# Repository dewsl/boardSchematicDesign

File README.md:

# boardSchematicDesign
Schematic , Board and SketchUp Files (sch,brd,skp files)

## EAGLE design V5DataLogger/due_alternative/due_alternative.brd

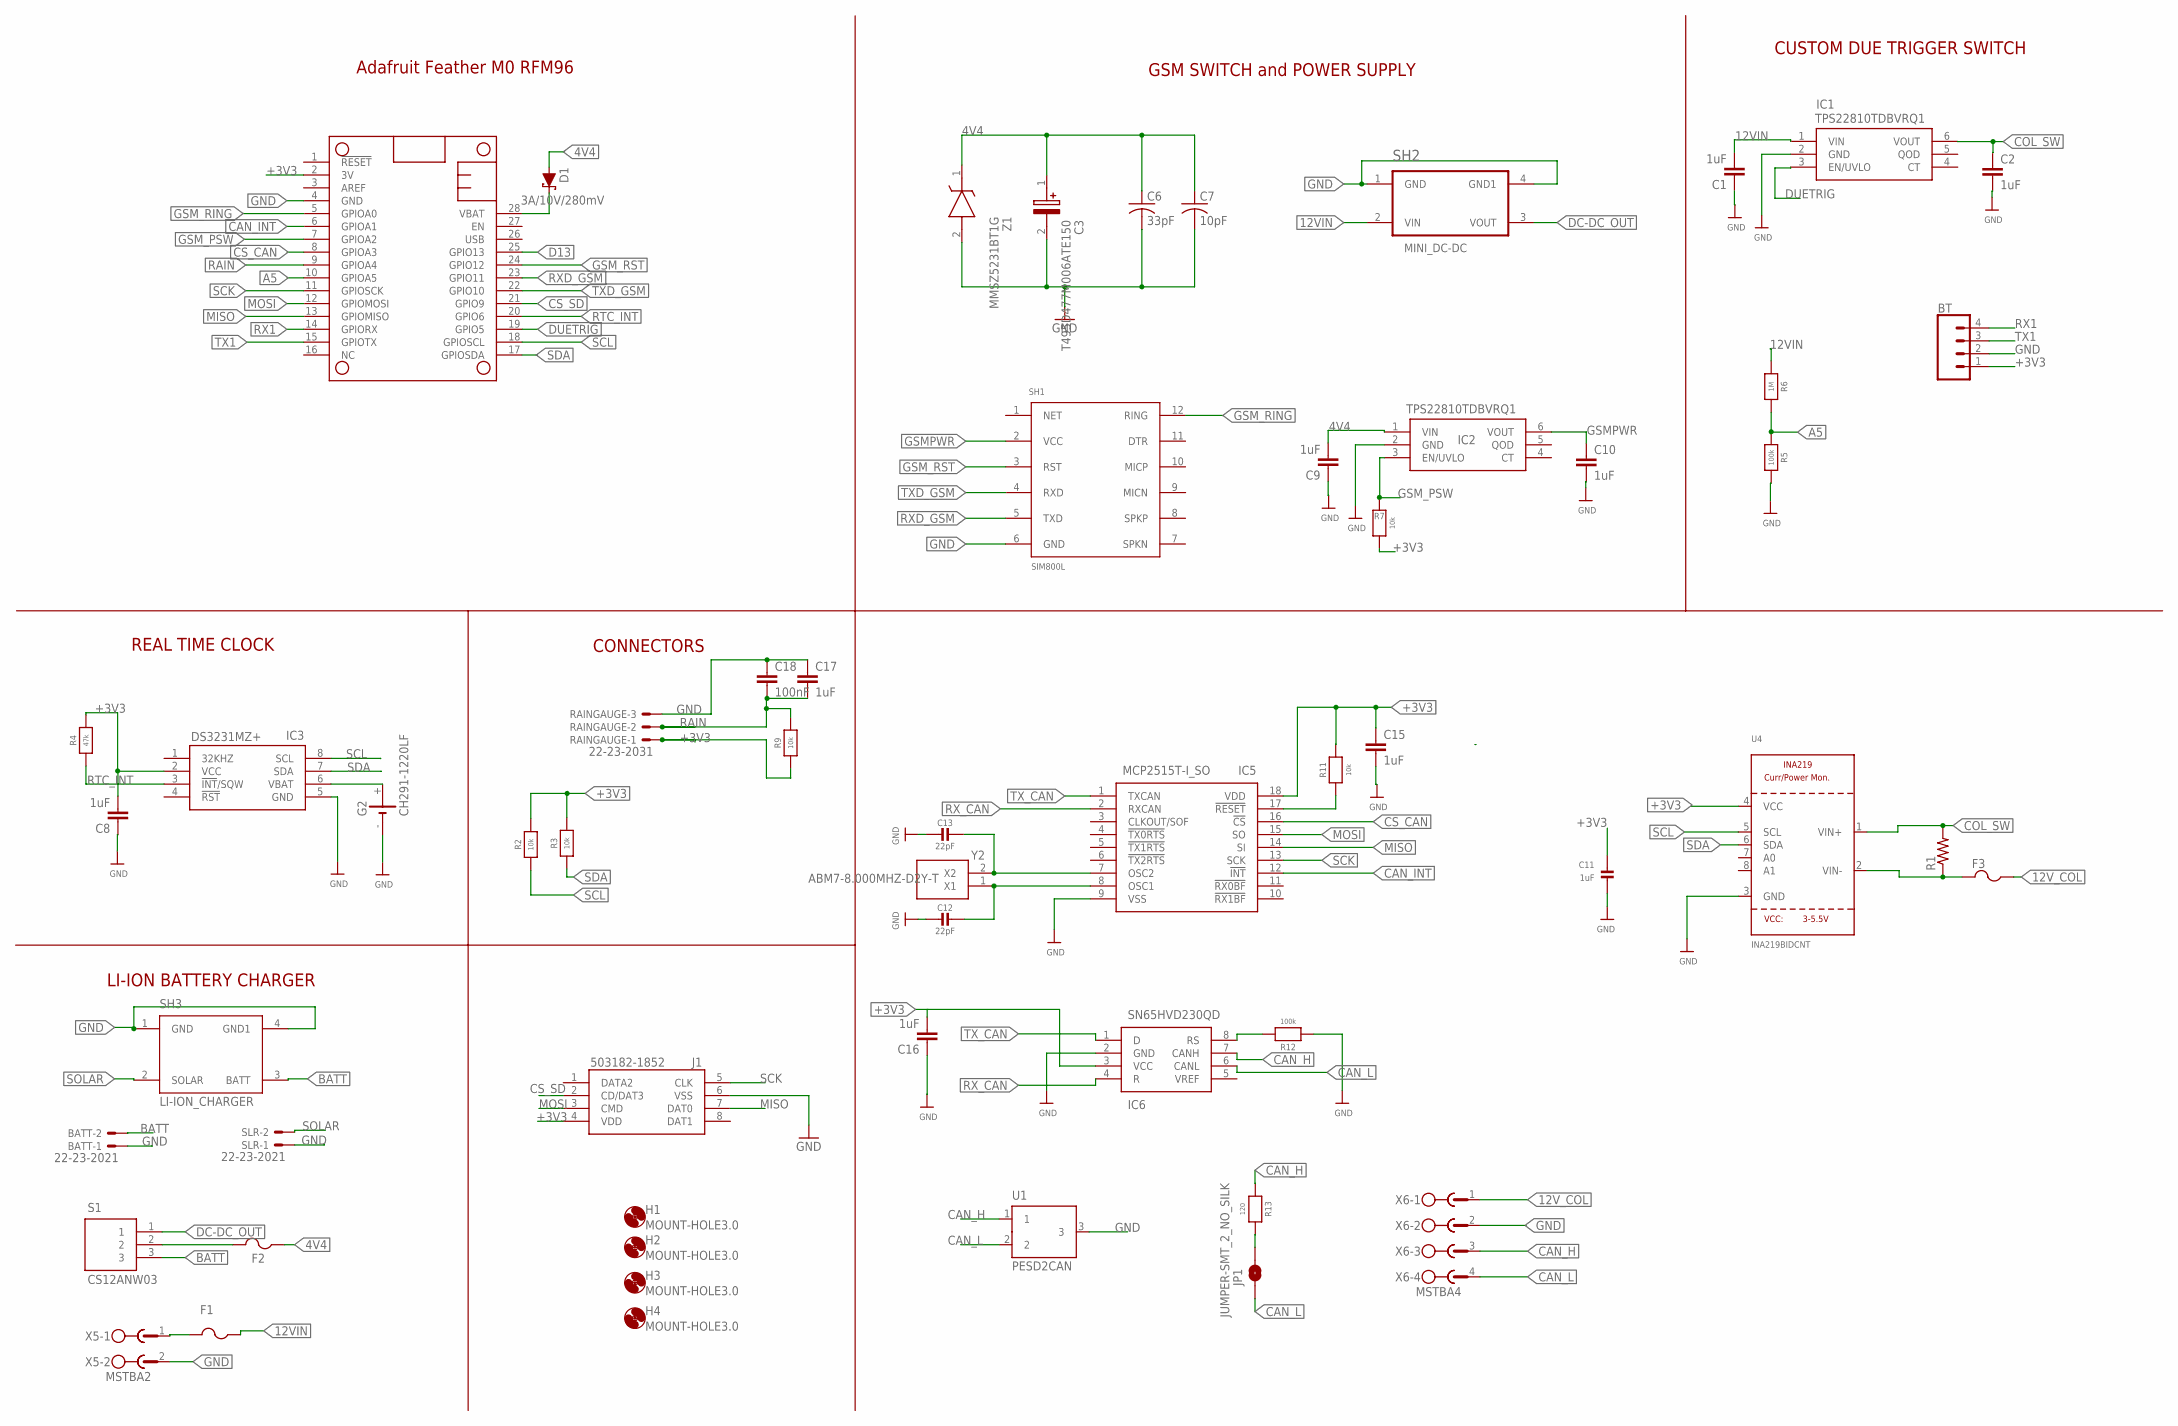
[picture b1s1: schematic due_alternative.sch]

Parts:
BATT: 22-23-2021
BT: CONN_04PTH; 1X04
C1, C2, C8, C9, C10, C15, C16, C17: 1uF; C0603
C3: T495D477M006ATE150; CAPPM7343X310N
C6: 33pF; C0603
C7: 10pF; C0603
C11: 1uF; 0603-NO
C12, C13: 22pF; 0603-NO
C18: 100nF; C0603
D1: 3A/10V/280mV; SOD-323
F1, F2, F3: PTCFUSE-1206; R1206
G2: CH291-1220LF
H1, H2, H3, H4: MOUNT-HOLE3.0; 3,0
IC1, IC2: TPS22810TDBVRQ1; SOT95P280X145-6N
IC3: DS3231MZ+; SOIC127P600X175-8N
IC5: MCP2515T-I_SO; SOIC127P1030X265-18N
IC6: SN65HVD230QD; SOIC127P600X175-8N
J1: 503182-1852; 5031821852
JP1: JUMPER-SMT_2_NO_SILK; SMT-JUMPER_2_NO_SILK
MS1: FEATHERWING_NODIM; FEATHERWING_DIM
R1: R-US_R6332; R6332
R2, R3, R7, R9, R11: 10k; 0603-NO
R4: 47k; 0603-NO
R5, R12: 100k; 0603-NO
R6: 1M; 0603-NO
R13: 120; 0603-NO
RAINGAUGE: 22-23-2031
S1: CS12ANW03
SH1: SIM800L; GSM_SIM800L
SH2: MINI_DC-DC; MINI_DC-DC_MP2307DN
SH3: LI-ION_CHARGER
SLR: 22-23-2021
U1: PESD2CAN; SOT23
U4: INA219BIDCNT; SOT23-8; MPN INA219BIDCNT
X5: MSTBA2
X6: MSTBA4
Y2: ABM7-8.000MHZ-D2Y-T; ABM78000MHZD2YT
Z1: MMSZ5231BT1G; SOD3716X135N

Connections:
4V4: C3.1 (+), C6.1, C7.1, C9.2, D1.A, F2.1, IC2.1 (VIN), Z1.1 (K)
12VIN: C1.2, F1.1, IC1.1 (VIN), R6.1, SH2.2 (VIN)
12V_COL: F3.1, X6.1
+3V3: BT.1, C8.2, C11.1, C15.1, C16.2, IC3.2 (VCC), IC5.18 (VDD), IC6.3 (VCC), J1.4 (VDD), MS1.2 (3V), R2.2, R3.2, R4.2, R7.1, R9.1, R11.2, RAINGAUGE.1, U4.4 (VCC)
A5: MS1.10 (GPIOA5), R5.1, R6.2
BATT: BATT.2, S1.3, SH3.3 (BATT)
CAN_H: IC6.7 (CANH), R13.1, U1.1, X6.3
CAN_INT: IC5.12 (!INT), MS1.6 (GPIOA1)
CAN_L: IC6.6 (CANL), JP1.1, U1.2, X6.4
COL_SW: C2.1, IC1.6 (VOUT), R1.2, U4.1 (VIN+)
CS_CAN: IC5.16 (!CS), MS1.8 (GPIOA3)
CS_SD: J1.2 (CD/DAT3), MS1.21 (GPIO9)
D13: MS1.25 (GPIO13)
DC-DC_OUT: S1.1, SH2.3 (VOUT)
DUETRIG: IC1.3 (EN/UVLO), MS1.19 (GPIO5)
GND: BATT.1, BT.2, C1.1, C2.2, C3.2 (-), C6.2, C7.2, C8.1, C9.1, C10.2, C11.2, C12.2, C13.2, C15.2, C16.1, C17.1, C18.1, G2.-, IC1.2 (GND), IC2.2 (GND), IC3.5 (GND), IC5.9 (VSS), IC6.2 (GND), J1.6 (VSS), MS1.4 (GND), R5.2, R12.1, RAINGAUGE.3, SH1.6 (GND), SH2.1 (GND), SH2.4 (GND1), SH3.1 (GND), SH3.4 (GND1), SLR.1, U1.3, U4.3 (GND), X5.2, X6.2, Z1.2 (A)
GSMPWR: C10.1, IC2.6 (VOUT), SH1.2 (VCC)
GSM_PSW: IC2.3 (EN/UVLO), MS1.7 (GPIOA2), R7.2
GSM_RING: MS1.5 (GPIOA0), SH1.12 (RING)
GSM_RST: MS1.24 (GPIO12), SH1.3 (RST)
MISO: IC5.14 (SI), J1.7 (DAT0), MS1.13 (GPIOMISO)
MOSI: IC5.15 (SO), J1.3 (CMD), MS1.12 (GPIOMOSI)
unnamed: C12.1, IC5.8 (OSC1), Y2.1 (X1)
unnamed: G2.+, IC3.6 (VBAT)
unnamed: C13.1, IC5.7 (OSC2), Y2.2 (X2)
unnamed: F1.2, X5.1
unnamed: IC6.8 (RS), R12.2
unnamed: F3.2, R1.1, U4.2 (VIN-)
unnamed: IC5.17 (!RESET), R11.1
unnamed: JP1.2, R13.2
unnamed: F2.2, S1.2
RAIN: C17.2, C18.2, MS1.9 (GPIOA4), R9.2, RAINGAUGE.2
RTC_INT: IC3.3 (!INT!/SQW), MS1.20 (GPIO6), R4.1
RX1: BT.4, MS1.14 (GPIORX)
RXD_GSM: MS1.23 (GPIO11), SH1.5 (TXD)
RX_CAN: IC5.2 (RXCAN), IC6.4 (R)
SCK: IC5.13 (SCK), J1.5 (CLK), MS1.11 (GPIOSCK)
SCL: IC3.8 (SCL), MS1.18 (GPIOSCL), R2.1, U4.5 (SCL)
SDA: IC3.7 (SDA), MS1.17 (GPIOSDA), R3.1, U4.6 (SDA)
SOLAR: SH3.2 (SOLAR), SLR.2
TX1: BT.3, MS1.15 (GPIOTX)
TXD_GSM: MS1.22 (GPIO10), SH1.4 (RXD)
TX_CAN: IC5.1 (TXCAN), IC6.1 (D)
VBAT: D1.C, MS1.28 (VBAT)

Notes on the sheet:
Adafruit Feather M0 RFM96
GSM SWITCH and POWER SUPPLY
CUSTOM DUE TRIGGER SWITCH
REAL TIME CLOCK
CONNECTORS
LI-ION BATTERY CHARGER

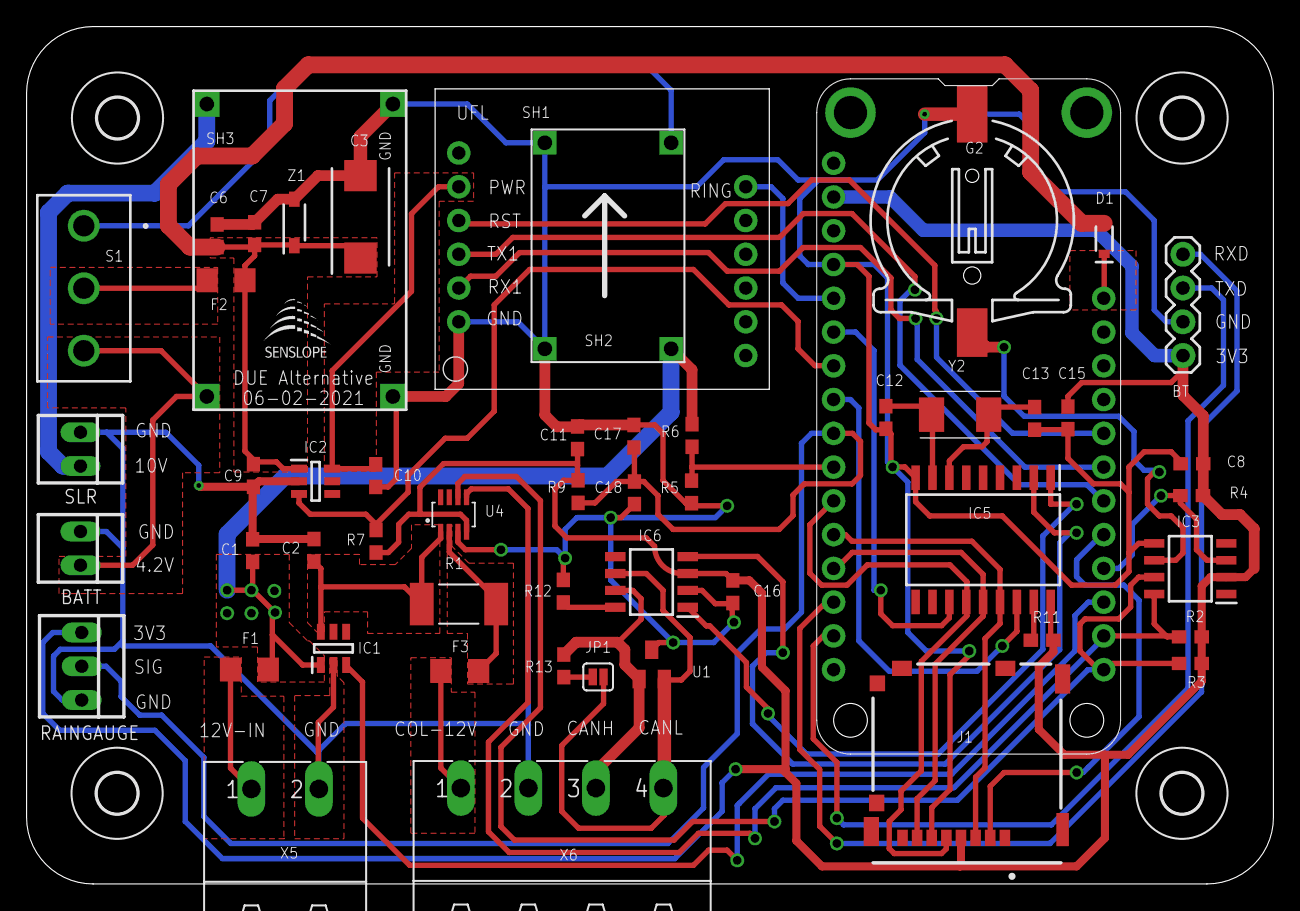
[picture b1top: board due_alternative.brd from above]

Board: 2 copper layers, 93.8 x 64.5 mm, 58 parts (0 on the bottom side), 43 nets.

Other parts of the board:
U$13: LOGO_SML_TNAME

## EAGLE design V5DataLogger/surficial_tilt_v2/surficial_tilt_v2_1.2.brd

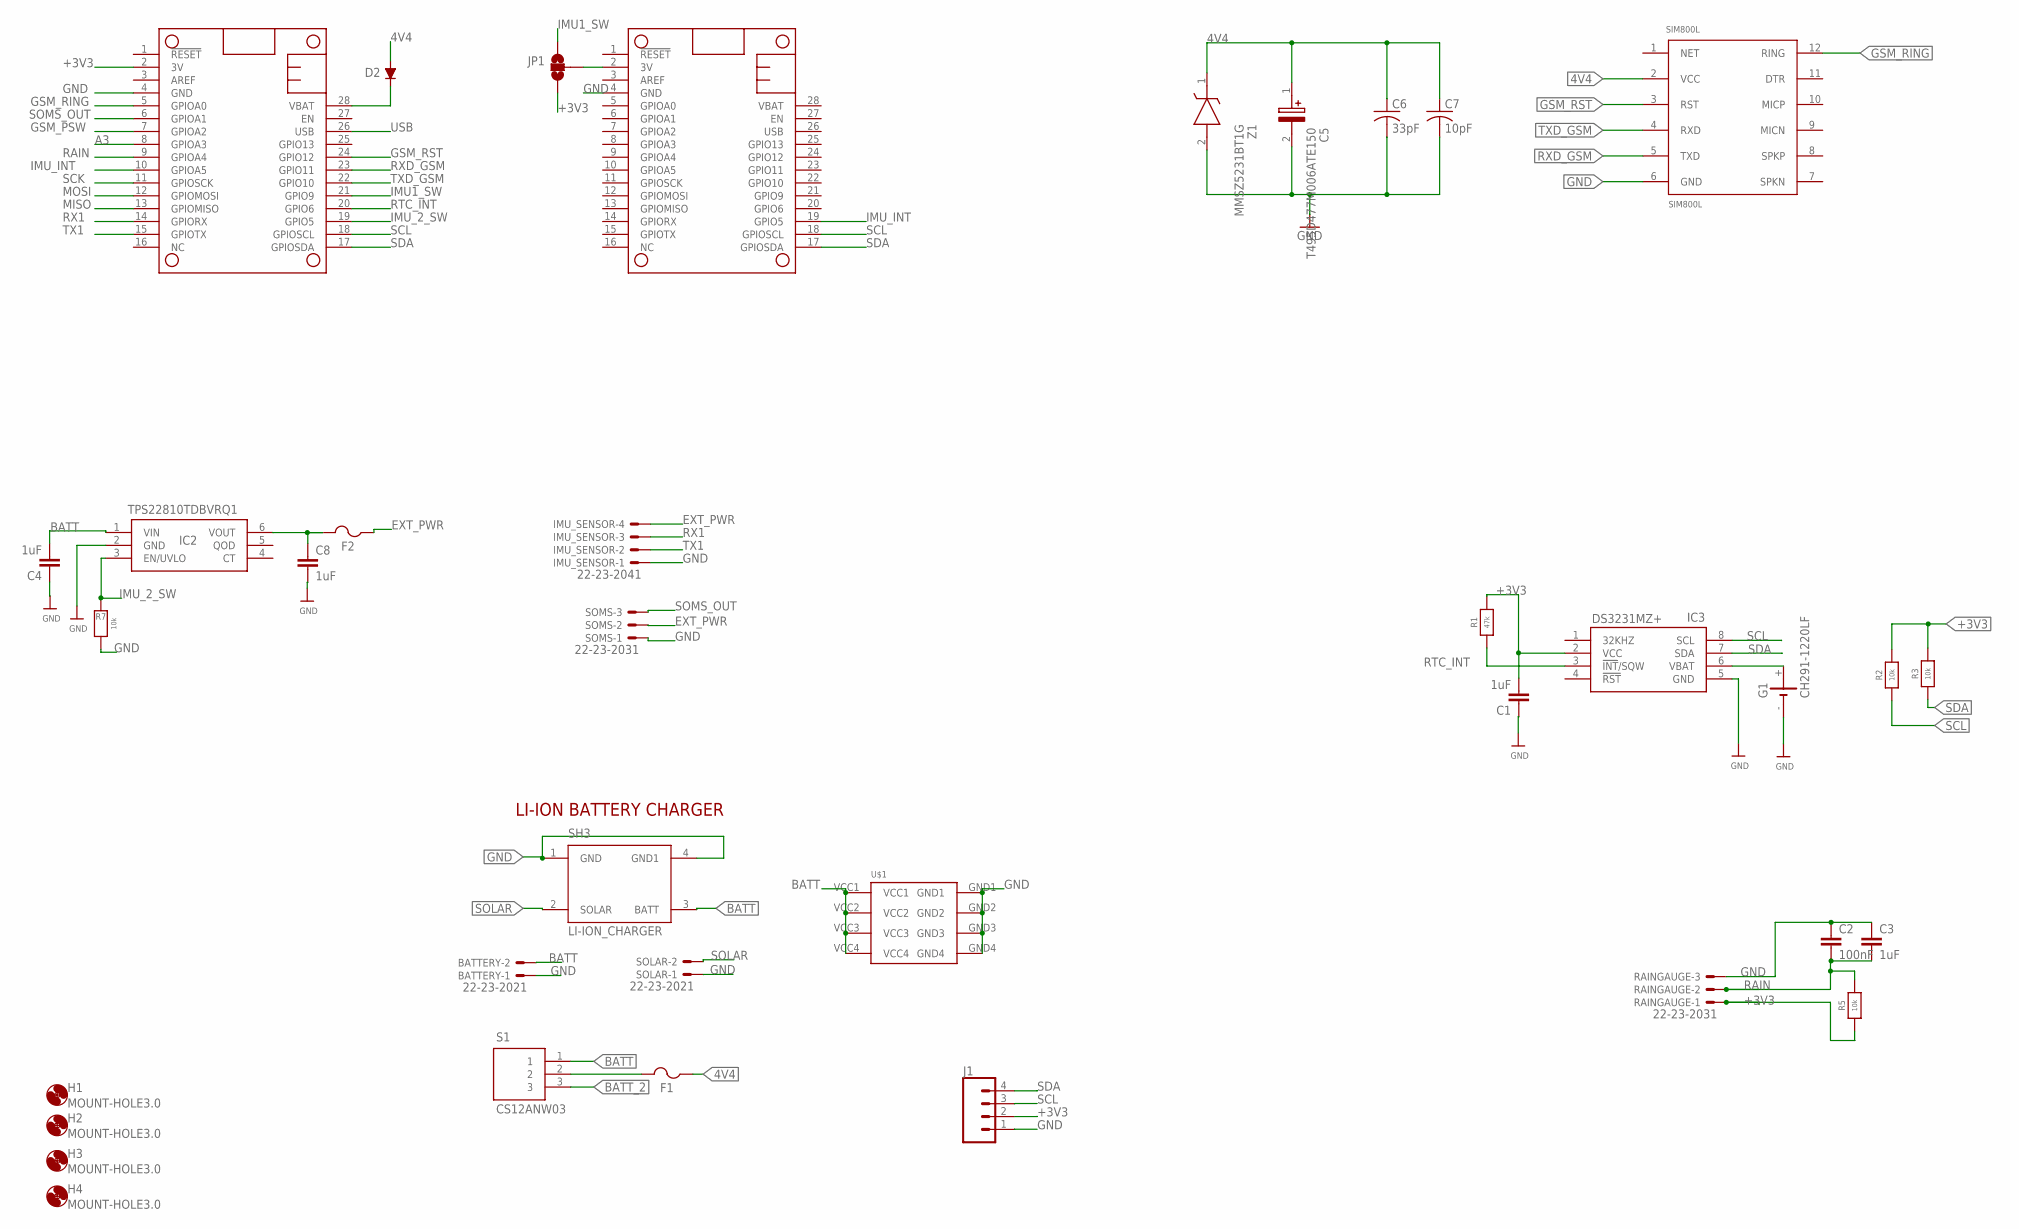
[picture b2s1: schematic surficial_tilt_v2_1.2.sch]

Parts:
BATTERY: 22-23-2021
C1, C3, C4, C8: 1uF; C0603
C2: 100nF; C0603
C5: T495D477M006ATE150; CAPPM7343X310N
C6: 33pF; C0603
C7: 10pF; C0603
D2: DIODE_DIODE-SOD123; DIODE_SOD123
F1, F2: PTCFUSE-1206; R1206
G1: CH291-1220LF
H1, H2, H3, H4: MOUNT-HOLE3.0; 3,0
IC2: TPS22810TDBVRQ1; SOT95P280X145-6N
IC3: DS3231MZ+; SOIC127P600X175-8N
IMU_SENSOR: 22-23-2041
J1: CONN_04PTH; 1X04
JP1: JUMPER-SMT_3_NO_SILK; SMT-JUMPER_3_NO_SILK
MS2, MS3: FEATHERWING_NODIM; FEATHERWING_DIM
R1: 47k; 0603-NO
R2, R3, R5, R7: 10k; 0603-NO
RAINGAUGE: 22-23-2031
S1: CS12ANW03
SH3: LI-ION_CHARGER
SIM800L: SIM800L; GSM_SIM800L
SOLAR: 22-23-2021
SOMS: 22-23-2031
U$1: 18650_HOLDER4_BATT_18650_BOTTOM; 4_BATT_18650_BOTTOM
Z1: MMSZ5231BT1G; SOD3716X135N

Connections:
3V: JP1.2, MS3.2 (3V)
4V4: C5.1 (+), C6.1, C7.1, D2.A, F1.1, SIM800L.2 (VCC), Z1.1 (K)
+3V3: C1.2, IC3.2 (VCC), J1.2, JP1.1, MS2.2 (3V), R1.2, R2.2, R3.2, R5.1, RAINGAUGE.1
A3: MS2.8 (GPIOA3)
BATT: BATTERY.2, C4.2, IC2.1 (VIN), S1.1, SH3.3 (BATT), U$1.VCC1, U$1.VCC2, U$1.VCC3, U$1.VCC4
BATT_2: S1.3
EXT_PWR: F2.1, IMU_SENSOR.4, SOMS.2
GND: BATTERY.1, C1.1, C2.1, C3.1, C4.1, C5.2 (-), C6.2, C7.2, C8.2, G1.-, IC2.2 (GND), IC3.5 (GND), IMU_SENSOR.1, J1.1, MS2.4 (GND), MS3.4 (GND), R7.1, RAINGAUGE.3, SH3.1 (GND), SH3.4 (GND1), SIM800L.6 (GND), SOLAR.1, SOMS.1, U$1.GND1, U$1.GND2, U$1.GND3, U$1.GND4, Z1.2 (A)
GSM_PSW: MS2.7 (GPIOA2)
GSM_RING: MS2.5 (GPIOA0), SIM800L.12 (RING)
GSM_RST: MS2.24 (GPIO12), SIM800L.3 (RST)
IMU1_SW: JP1.3, MS2.21 (GPIO9)
IMU_2_SW: IC2.3 (EN/UVLO), MS2.19 (GPIO5), R7.2
IMU_INT: MS2.10 (GPIOA5), MS3.19 (GPIO5)
MISO: MS2.13 (GPIOMISO)
MOSI: MS2.12 (GPIOMOSI)
unnamed: C8.1, F2.2, IC2.6 (VOUT)
unnamed: G1.+, IC3.6 (VBAT)
unnamed: F1.2, S1.2
RAIN: C2.2, C3.2, MS2.9 (GPIOA4), R5.2, RAINGAUGE.2
RTC_INT: IC3.3 (!INT!/SQW), MS2.20 (GPIO6), R1.1
RX1: IMU_SENSOR.3, MS2.14 (GPIORX)
RXD_GSM: MS2.23 (GPIO11), SIM800L.5 (TXD)
SCK: MS2.11 (GPIOSCK)
SCL: IC3.8 (SCL), J1.3, MS2.18 (GPIOSCL), MS3.18 (GPIOSCL), R2.1
SDA: IC3.7 (SDA), J1.4, MS2.17 (GPIOSDA), MS3.17 (GPIOSDA), R3.1
SOLAR: SH3.2 (SOLAR), SOLAR.2
SOMS_OUT: MS2.6 (GPIOA1), SOMS.3
TX1: IMU_SENSOR.2, MS2.15 (GPIOTX)
TXD_GSM: MS2.22 (GPIO10), SIM800L.4 (RXD)
USB: MS2.26 (USB)
VBAT: D2.C, MS2.28 (VBAT)

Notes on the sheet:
LI-ION BATTERY CHARGER

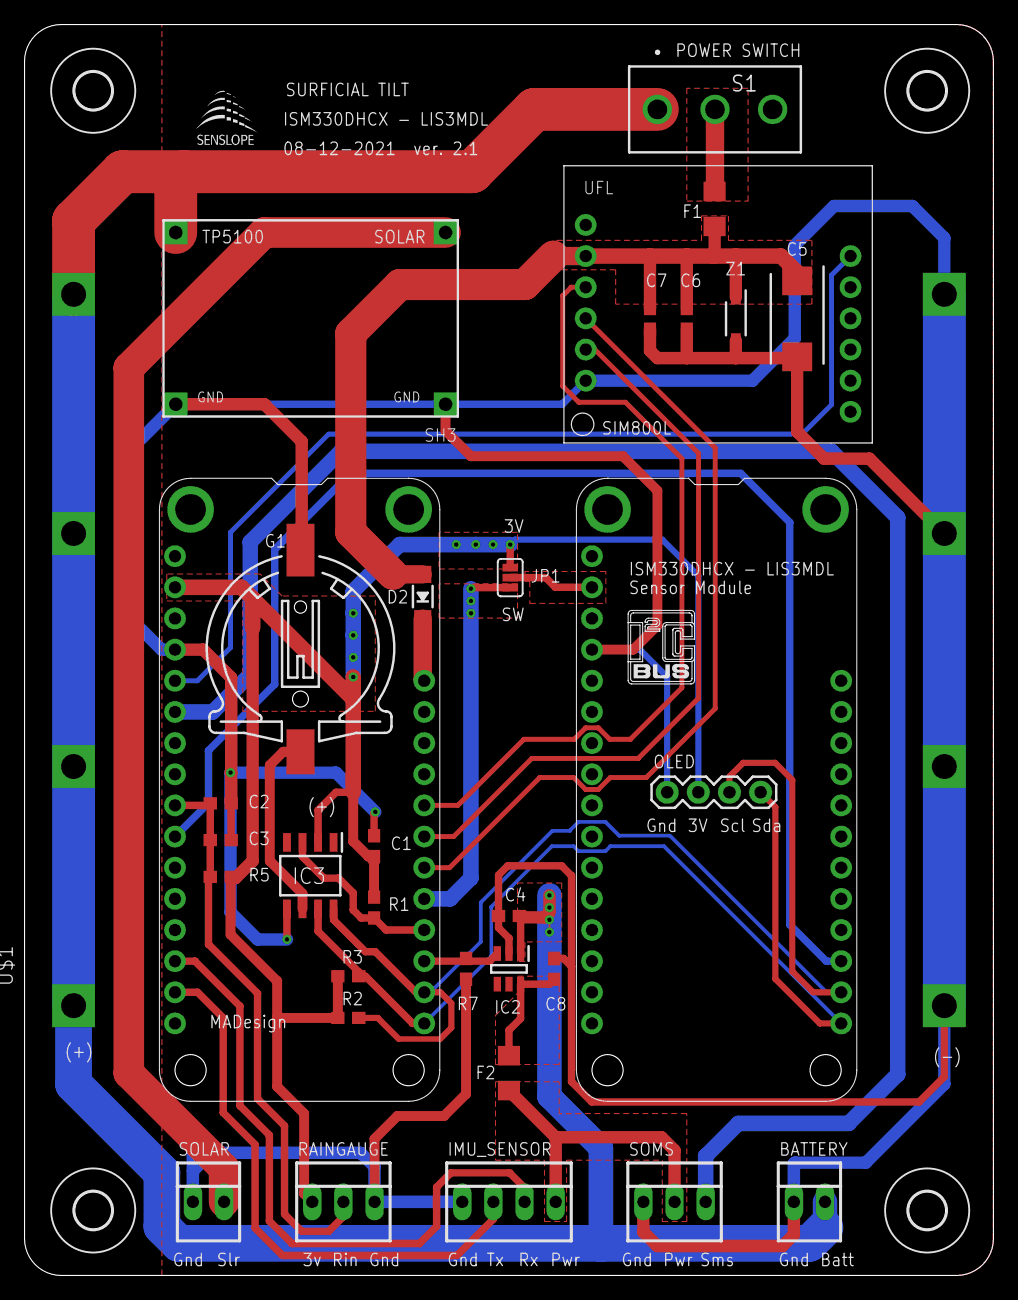
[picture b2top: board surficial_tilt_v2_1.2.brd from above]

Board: 2 copper layers, 79.0 x 102.0 mm, 40 parts (0 on the bottom side), 25 nets.

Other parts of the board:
U$2: LOGO
U$3: I2C
U$13: LOGO_SML_TNAME

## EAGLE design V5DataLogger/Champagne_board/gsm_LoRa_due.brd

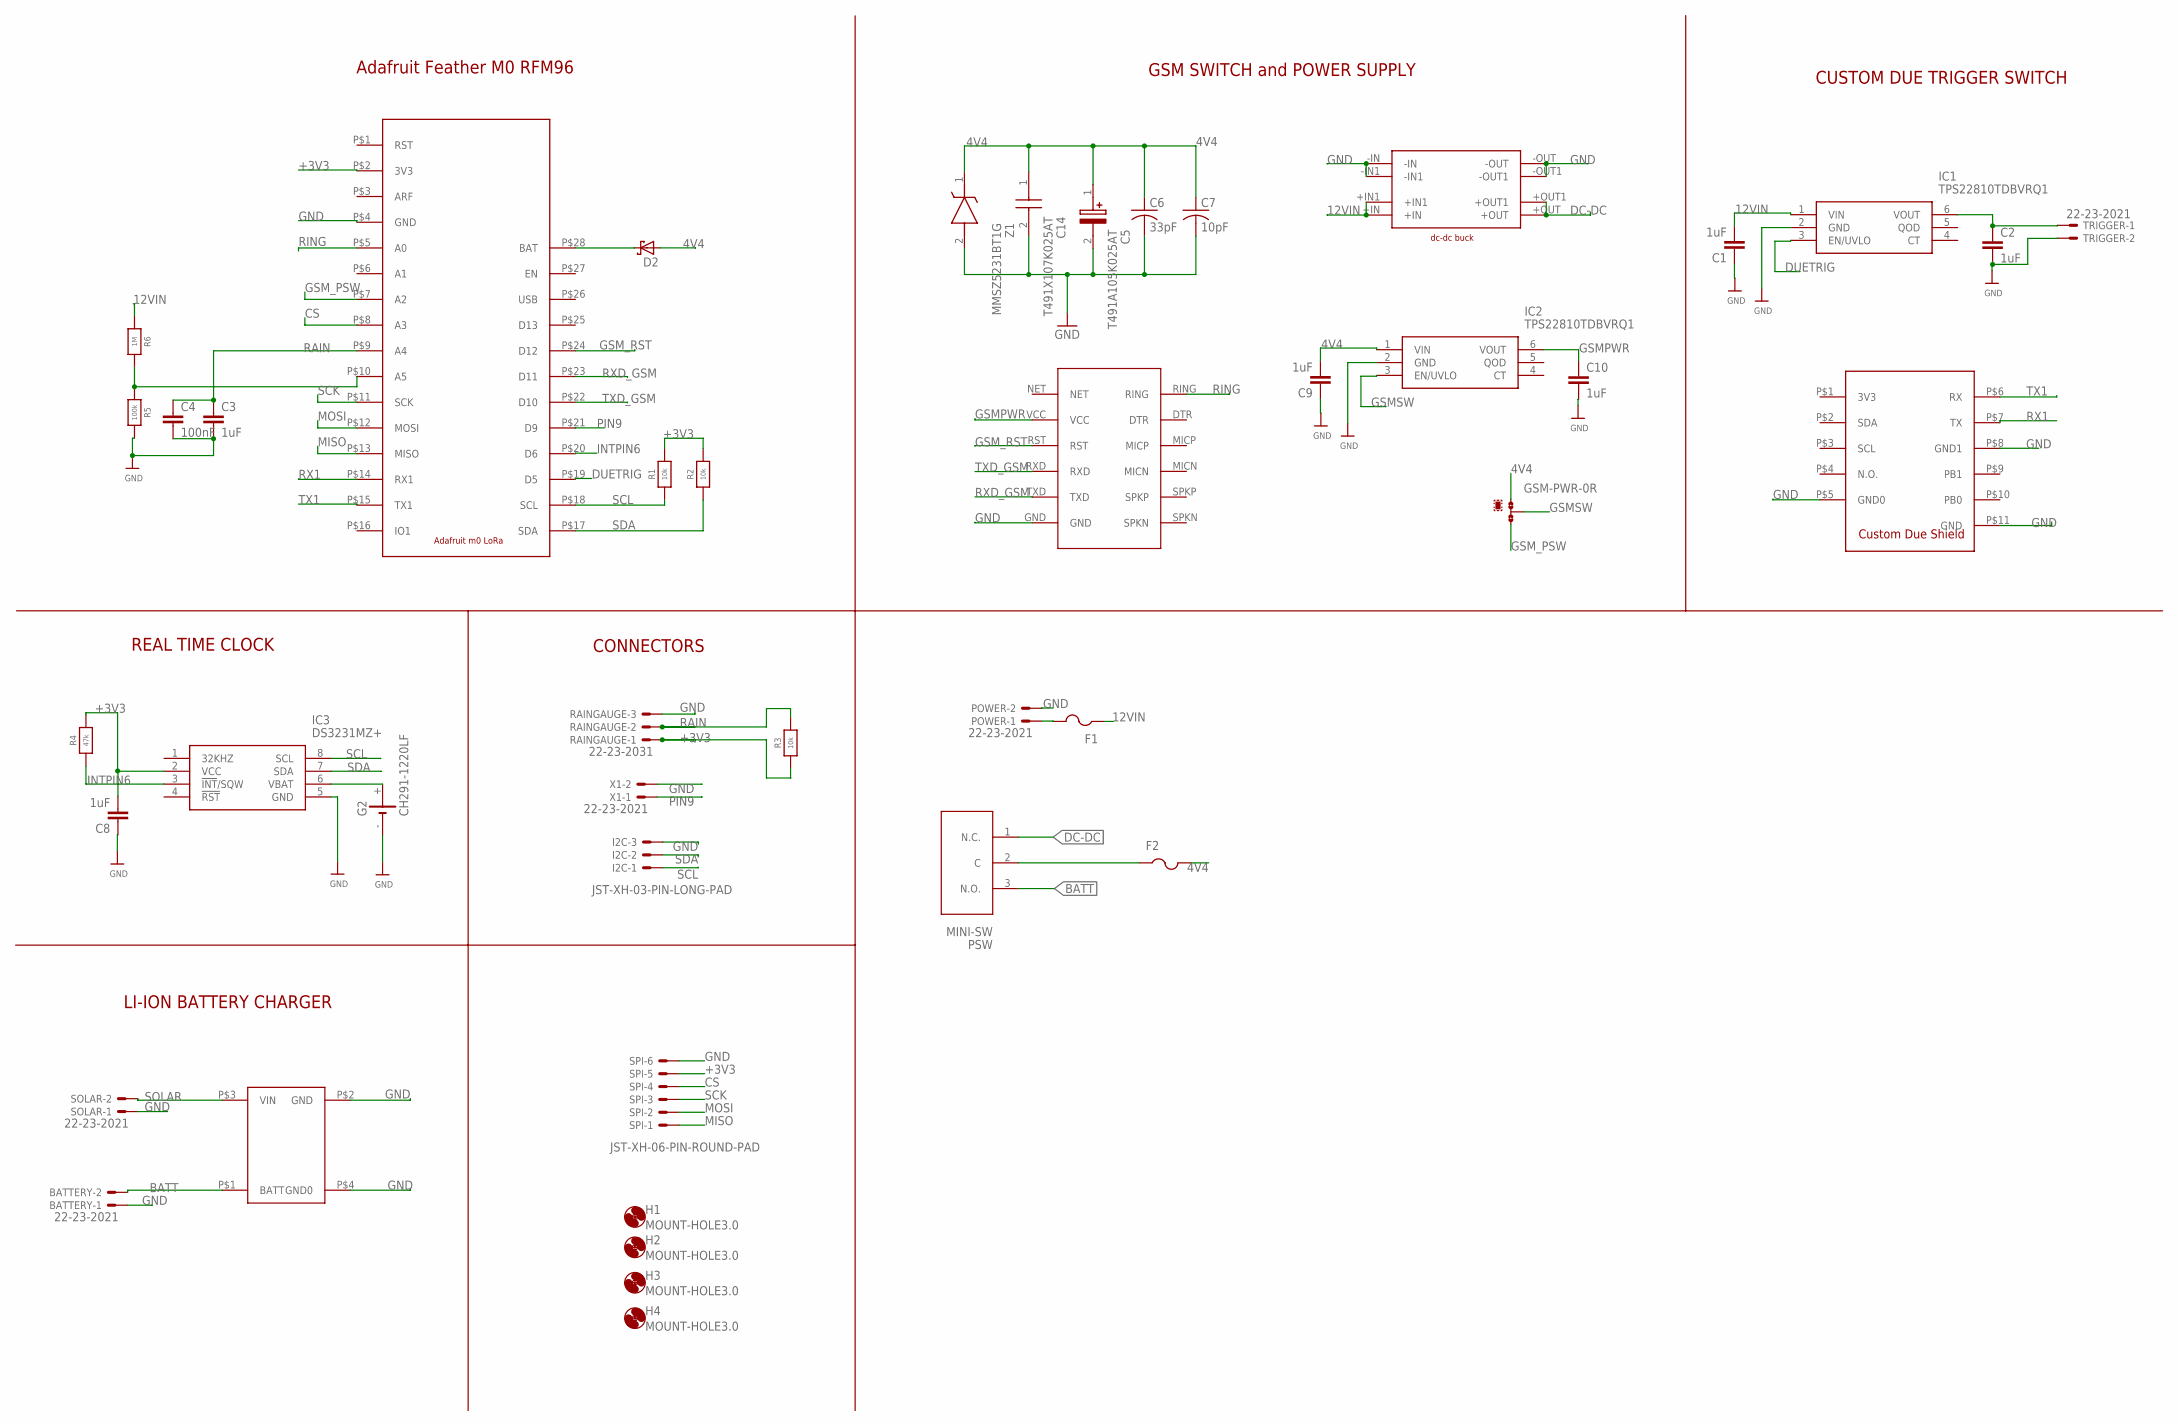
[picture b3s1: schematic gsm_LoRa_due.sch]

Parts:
BATTERY: 22-23-2021
C1, C2, C3, C8, C9, C10: 1uF; C0603
C4: 100nF; C0603
C5: T491A105K025AT; CAPPM3216X180N
C6: 33pF; C0603
C7: 10pF; C0603
C14: T491X107K025AT; CAPPM7343X430N
D2: SCHOTTKY-DIODE; DIODE_SMB
F1, F2: PTCFUSE-1206; R1206
G2: CH291-1220LF
GSM-PWR: 0R-JUMPB; B0R-JMP
H1, H2, H3, H4: MOUNT-HOLE3.0; 3,0
I2C: JST-XH-03-PIN-LONG-PAD; JST-XH-03-PACKAGE-LONG-PAD
IC1, IC2: TPS22810TDBVRQ1; SOT95P280X145-6N
IC3: DS3231MZ+; SOIC127P600X175-8N
POWER: 22-23-2021
PSW: MINI-SW
R1, R2, R3: 10k; 0603-NO
R4: 47k; 0603-NO
R5: 100k; 0603-NO
R6: 1M; 0603-NO
RAINGAUGE: 22-23-2031
SOLAR: 22-23-2021
SPI: JST-XH-06-PIN-ROUND-PAD; JST-XH-06-PACKAGE-ROUND-PAD
TRIGGER: 22-23-2021
U$1: M0_LORA; RFM69
U$8: DUE_PADSDUE_GSM; DUESHIELD_BIG
U$9: SIM800L_MODULE; SIM800L
U$10: DC-DC_BUCK_MAD; DC-DC_BUCK
U$11: LI-ION-CHARGER; LI-ION
X1: 22-23-2021
Z1: MMSZ5231BT1G; SOD3716X135N

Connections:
4V4: C5.1 (+), C6.1, C7.1, C9.2, C14.1, D2.A (C), F2.2, GSM-PWR.1, IC2.1 (VIN), Z1.1 (K)
12VIN: C1.2, F1.1, IC1.1 (VIN), R6.1, U$10.+IN, U$10.+IN1
+3V3: C8.2, IC3.2 (VCC), R1.2, R2.2, R3.1, R4.2, RAINGAUGE.1, SPI.5, U$1.P$2 (3V3)
BATT: BATTERY.2, PSW.3 (N.O.), U$11.P$1 (BATT)
CS: SPI.4, U$1.P$8 (A3)
DC-DC: PSW.1 (N.C.), U$10.+OUT, U$10.+OUT1
DUETRIG: IC1.3 (EN/UVLO), U$1.P$19 (D5)
GND: BATTERY.1, C1.1, C2.2, C3.2, C4.2, C5.2 (-), C6.2, C7.2, C8.1, C9.1, C10.2, C14.2, G2.-, I2C.3, IC1.2 (GND), IC2.2 (GND), IC3.5 (GND), POWER.2, R5.2, RAINGAUGE.3, SOLAR.1, SPI.6, TRIGGER.2, U$1.P$4 (GND), U$8.P$5 (GND0), U$8.P$8 (GND1), U$8.P$11 (GND), U$9.GND, U$10.-IN, U$10.-IN1, U$10.-OUT, U$10.-OUT1, U$11.P$2 (GND), U$11.P$4 (GND0), X1.2, Z1.2 (A)
GSMPWR: C10.1, IC2.6 (VOUT), U$9.VCC
GSMSW: GSM-PWR.2, IC2.3 (EN/UVLO)
GSM_PSW: GSM-PWR.3, U$1.P$7 (A2)
GSM_RST: U$1.P$24 (D12), U$9.RST
INTPIN6: IC3.3 (!INT!/SQW), R4.1, U$1.P$20 (D6)
MISO: SPI.1, U$1.P$13 (MISO)
MOSI: SPI.2, U$1.P$12 (MOSI)
unnamed: D2.C (A), U$1.P$28 (BAT)
unnamed: G2.+, IC3.6 (VBAT)
unnamed: F1.2, POWER.1
unnamed: R5.1, R6.2, U$1.P$10 (A5)
unnamed: F2.1, PSW.2 (C)
unnamed: C2.1, IC1.6 (VOUT), TRIGGER.1
PIN9: U$1.P$21 (D9), X1.1
RAIN: C3.1, C4.1, R3.2, RAINGAUGE.2, U$1.P$9 (A4)
RING: U$1.P$5 (A0), U$9.RING
RX1: U$1.P$14 (RX1), U$8.P$7 (TX)
RXD_GSM: U$1.P$23 (D11), U$9.TXD
SCK: SPI.3, U$1.P$11 (SCK)
SCL: I2C.1, IC3.8 (SCL), R1.1, U$1.P$18 (SCL)
SDA: I2C.2, IC3.7 (SDA), R2.1, U$1.P$17 (SDA)
SOLAR: SOLAR.2, U$11.P$3 (VIN)
TX1: U$1.P$15 (TX1), U$8.P$6 (RX)
TXD_GSM: U$1.P$22 (D10), U$9.RXD

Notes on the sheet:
Adafruit Feather M0 RFM96
GSM SWITCH and POWER SUPPLY
CUSTOM DUE TRIGGER SWITCH
REAL TIME CLOCK
CONNECTORS
LI-ION BATTERY CHARGER

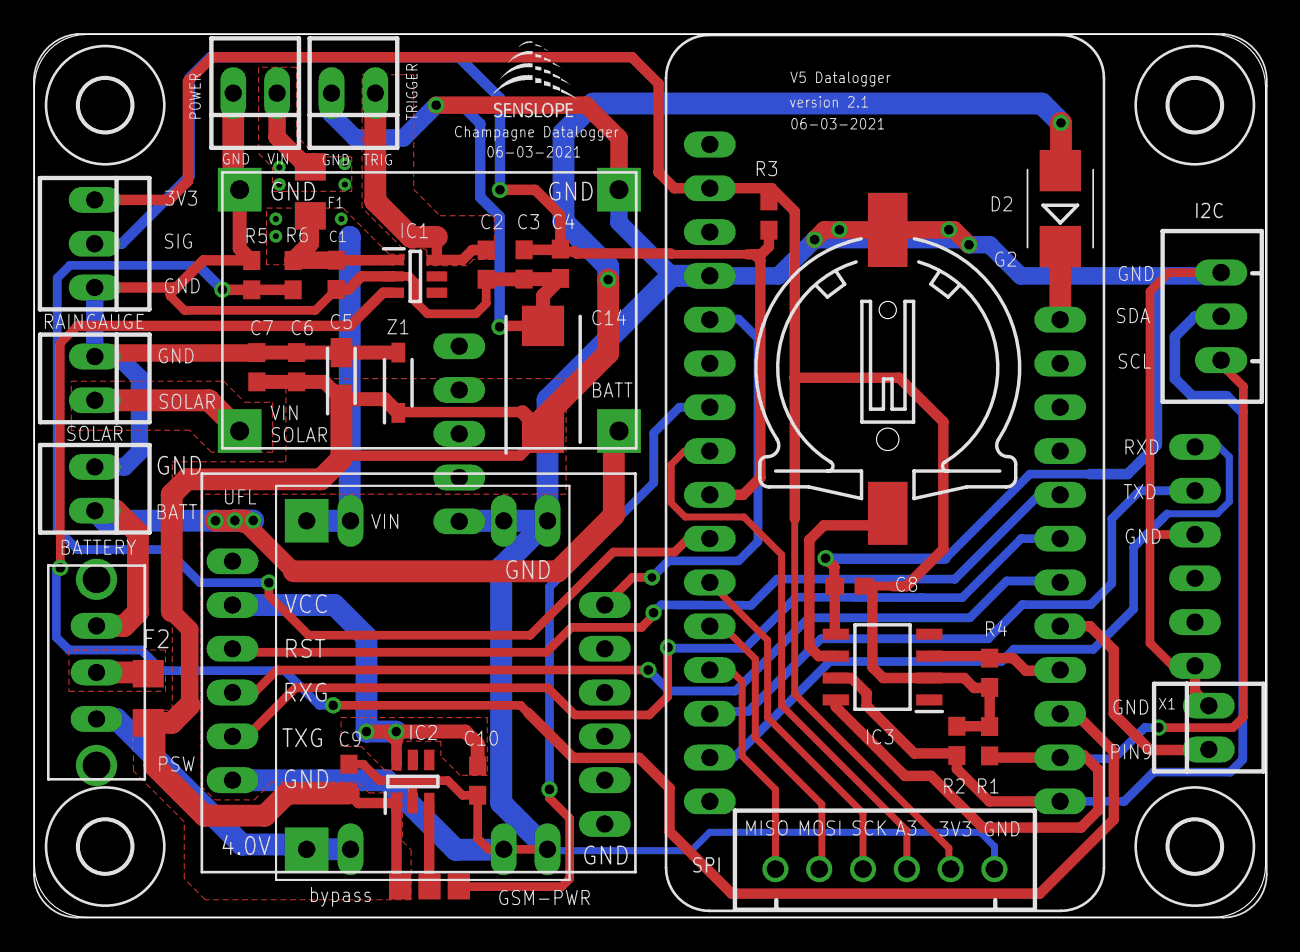
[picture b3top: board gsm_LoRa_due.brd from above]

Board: 2 copper layers, 71.4 x 51.2 mm, 45 parts (0 on the bottom side), 32 nets.

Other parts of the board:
U$13: LOGO_SML_TNAME

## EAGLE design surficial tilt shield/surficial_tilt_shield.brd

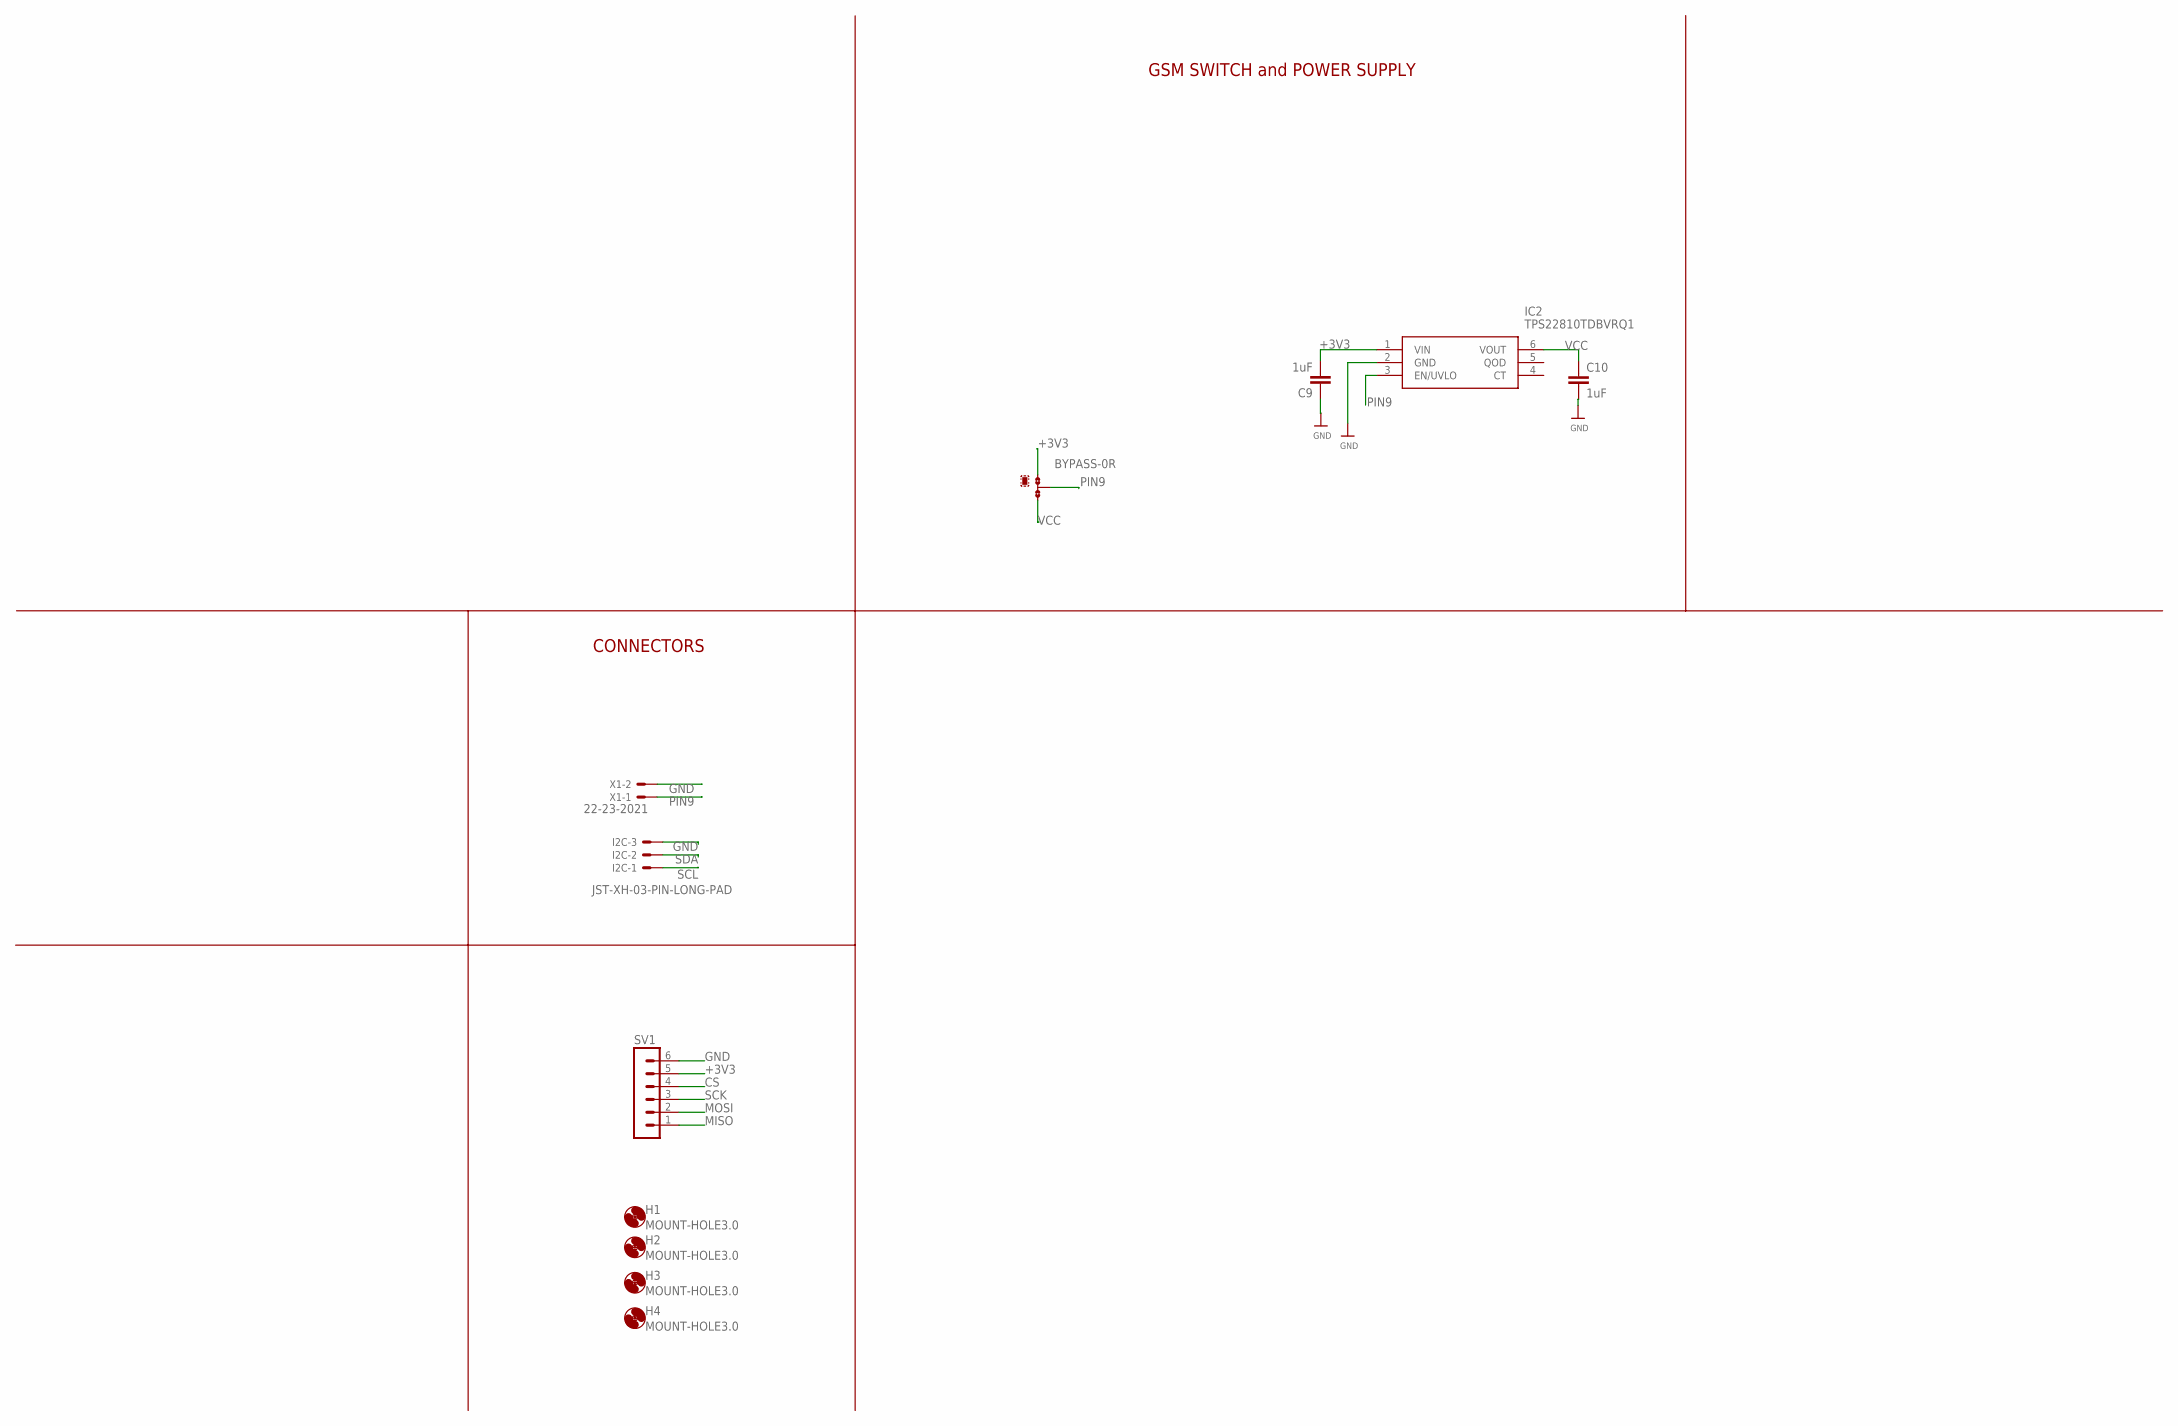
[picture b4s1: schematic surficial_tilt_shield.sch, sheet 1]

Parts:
BYPASS: 0R-JUMPB; B0R-JMP
C9, C10: 1uF; C0603
H1, H2, H3, H4: MOUNT-HOLE3.0; 3,0
I2C: JST-XH-03-PIN-LONG-PAD; JST-XH-03-PACKAGE-LONG-PAD
IC2: TPS22810TDBVRQ1; SOT95P280X145-6N
SV1: MA06-1
X1: 22-23-2021

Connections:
+3V3: BYPASS.1, C9.2, IC2.1 (VIN), SV1.5
CS: SV1.4
GND: C9.1, C10.2, I2C.3, IC2.2 (GND), SV1.6, X1.2; also elsewhere on the board
MISO: SV1.1
MOSI: SV1.2
PIN9: BYPASS.2, IC2.3 (EN/UVLO), X1.1
SCK: SV1.3
SCL: I2C.1; also elsewhere on the board
SDA: I2C.2; also elsewhere on the board
VCC: BYPASS.3, C10.1, IC2.6 (VOUT); also elsewhere on the board

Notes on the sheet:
GSM SWITCH and POWER SUPPLY
CONNECTORS

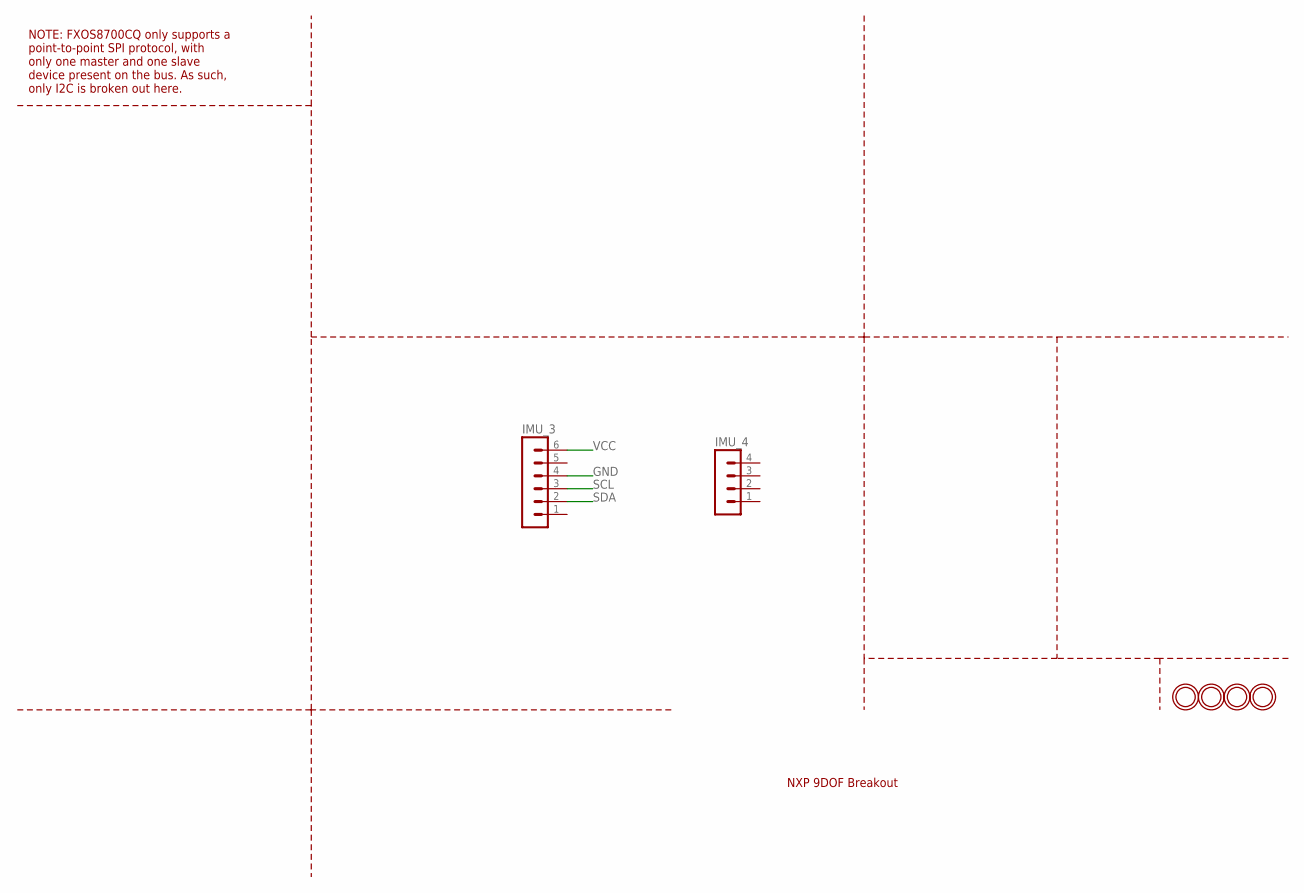
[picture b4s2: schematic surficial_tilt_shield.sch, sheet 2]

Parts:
IMU_3: MA06-1
IMU_4: MA04-1
U$1, U$2, U$3, U$4: MOUNTINGHOLE2.5; MOUNTINGHOLE_2.5_PLATED

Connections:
GND: IMU_3.4; also elsewhere on the board
SCL: IMU_3.3; also elsewhere on the board
SDA: IMU_3.2; also elsewhere on the board
VCC: IMU_3.6; also elsewhere on the board

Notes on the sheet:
NXP 9DOF Breakout
NOTE: FXOS8700CQ only supports a point-to-point SPI protocol, with only one master and one slave device present on the bus. As such, only I2C is broken out here.

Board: 2 copper layers, 18 parts (4 on the bottom side), 6 nets, no tracks yet.

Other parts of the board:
U$13: LOGO_SML_TNAME

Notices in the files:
parts and their libraries:
SparkFun-Connectors: Licensing: CC v3.0 Share-Alike You are welcome to use this library for commercial purposes.
microbuilder: This work is placed in the public domain, and may be freely used for commercial and non-commercial work with the following conditions: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
